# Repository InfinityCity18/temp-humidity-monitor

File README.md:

# Temperature and humidity HTTP monitor

A device that sends data about temperature and humidity to a HTTP server.
Also shows it on the lcd in daylight.

wokwi: https://wokwi.com/projects/406248125121901569

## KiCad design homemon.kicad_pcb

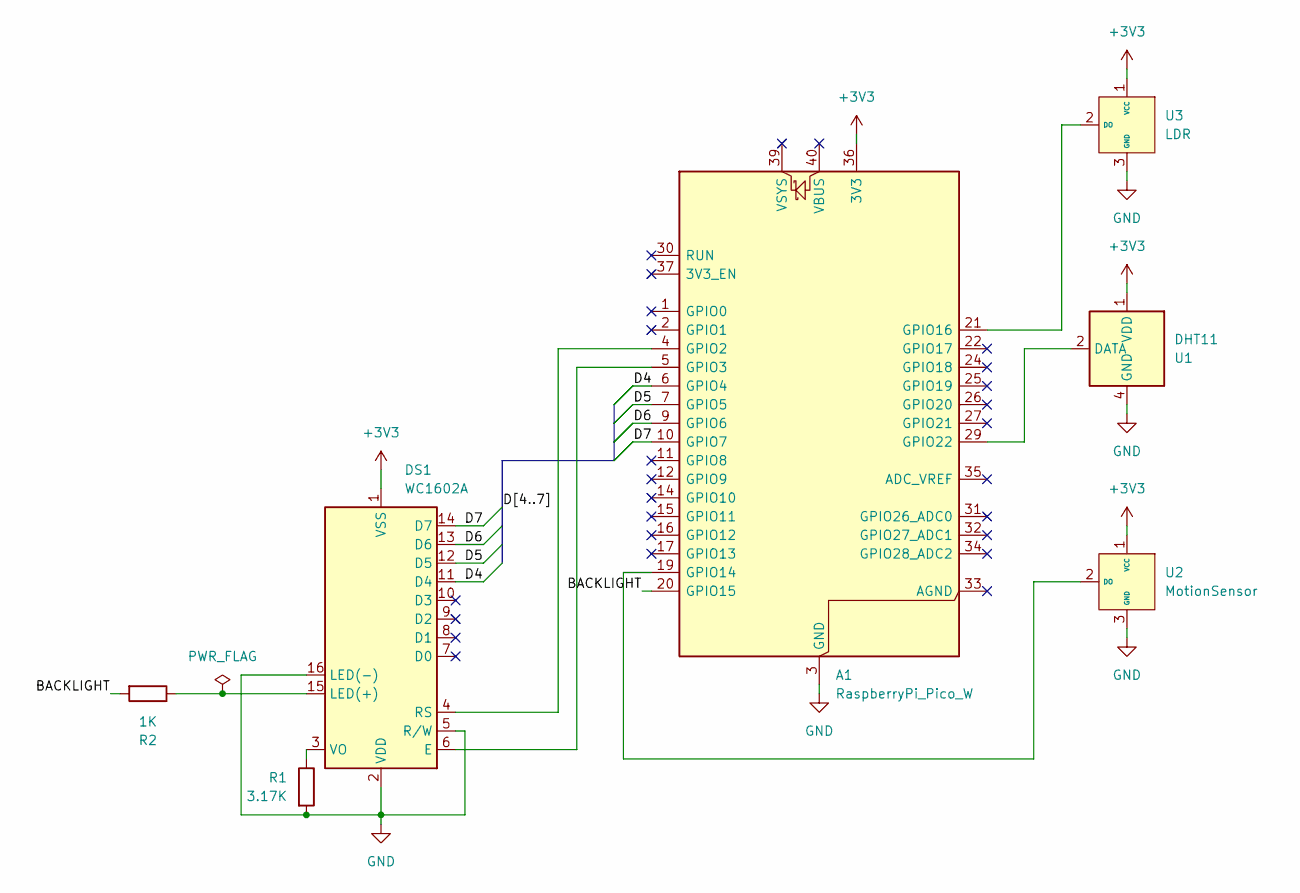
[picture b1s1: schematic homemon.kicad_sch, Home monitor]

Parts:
A1: RaspberryPi_Pico_W; RaspberryPi_Pico_Common_THT
DS1: WC1602A
R1: 3.17K; R_Axial_DIN0207_L6.3mm_D2.5mm_P10.16mm_Horizontal
R2: 1K; R_Axial_DIN0207_L6.3mm_D2.5mm_P10.16mm_Horizontal
U1: DHT11; PinHeader_1x03_P2.54mm_Vertical
U2: MotionSensor
U3: LDR; PinHeader_1x03_P2.54mm_Vertical

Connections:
+3V3: A1.36 (3V3), DS1.1 (VSS), U1.1 (VDD), U2.1 (VCC), U3.1 (VCC)
/BACKLIGHT: A1.20 (GPIO15), R2.2
/D4: A1.6 (GPIO4), DS1.11 (D4)
/D5: A1.7 (GPIO5), DS1.12 (D5)
/D6: A1.9 (GPIO6), DS1.13 (D6)
/D7: A1.10 (GPIO7), DS1.14 (D7)
GND: A1.3 (GND), A1.8 (GND), A1.13 (GND), A1.18 (GND), A1.23 (GND), A1.28 (GND), A1.38 (GND), DS1.2 (VDD), DS1.5 (R/W), DS1.16 (LED(-)), R1.2, U1.4 (GND), U2.3 (GND), U3.3 (GND)
unnamed: A1.4 (GPIO2), DS1.4 (RS)
unnamed: A1.5 (GPIO3), DS1.6 (E)
unnamed: A1.19 (GPIO14), U2.2 (DO)
unnamed: A1.21 (GPIO16), U3.2 (DO)
unnamed: A1.29 (GPIO22), U1.2 (DATA)
unnamed: DS1.15 (LED(+)), R2.1
unnamed: DS1.3 (VO), R1.1

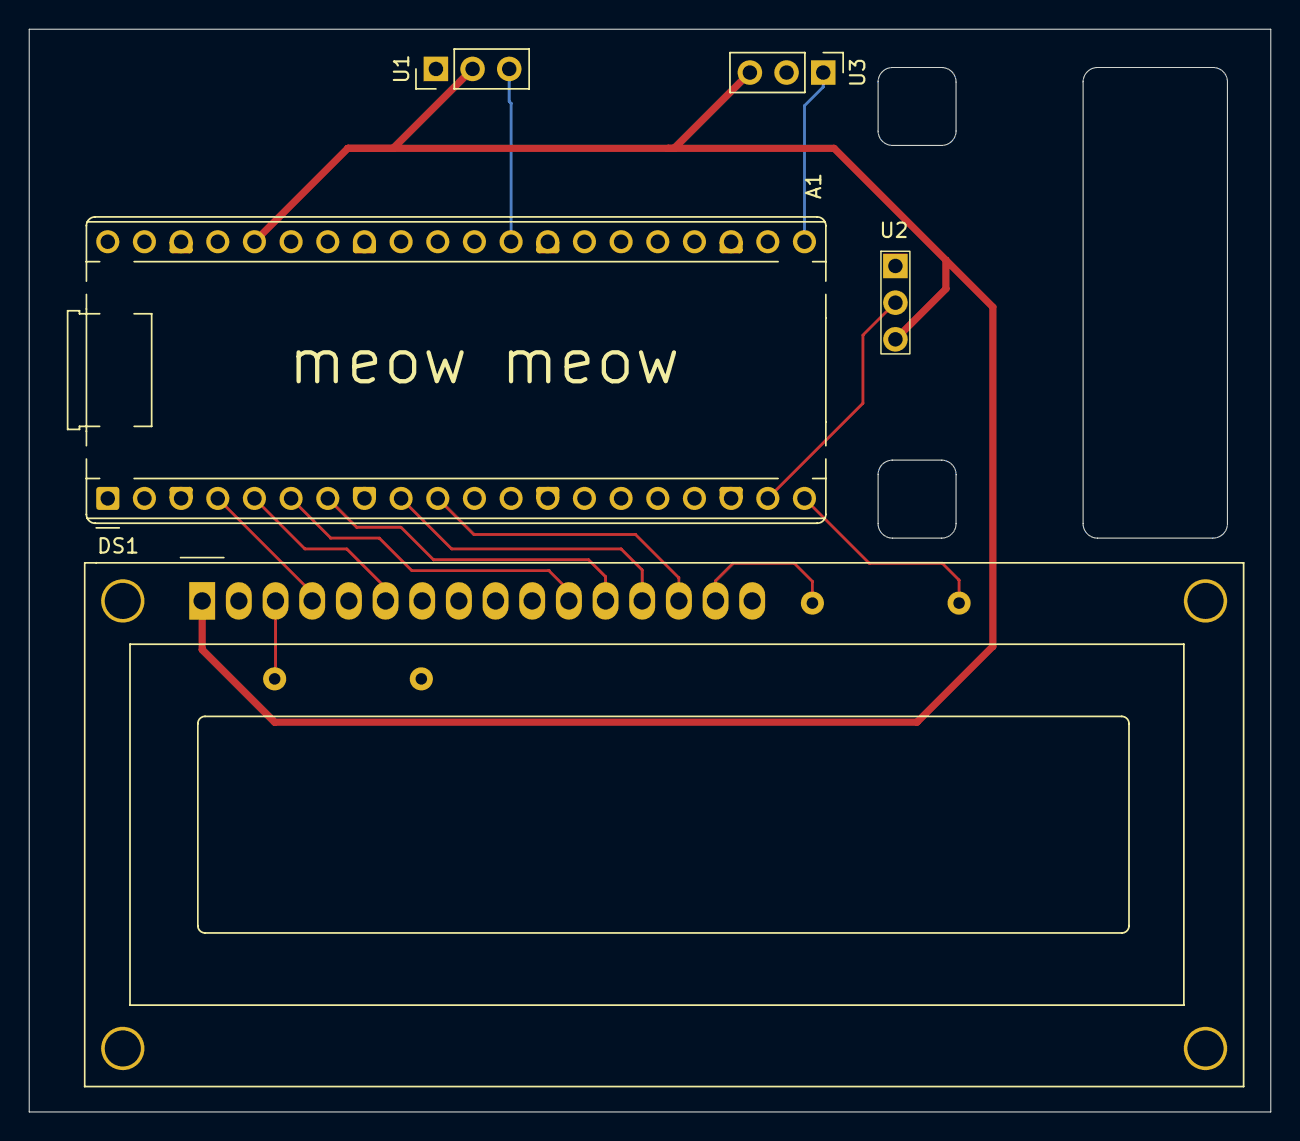
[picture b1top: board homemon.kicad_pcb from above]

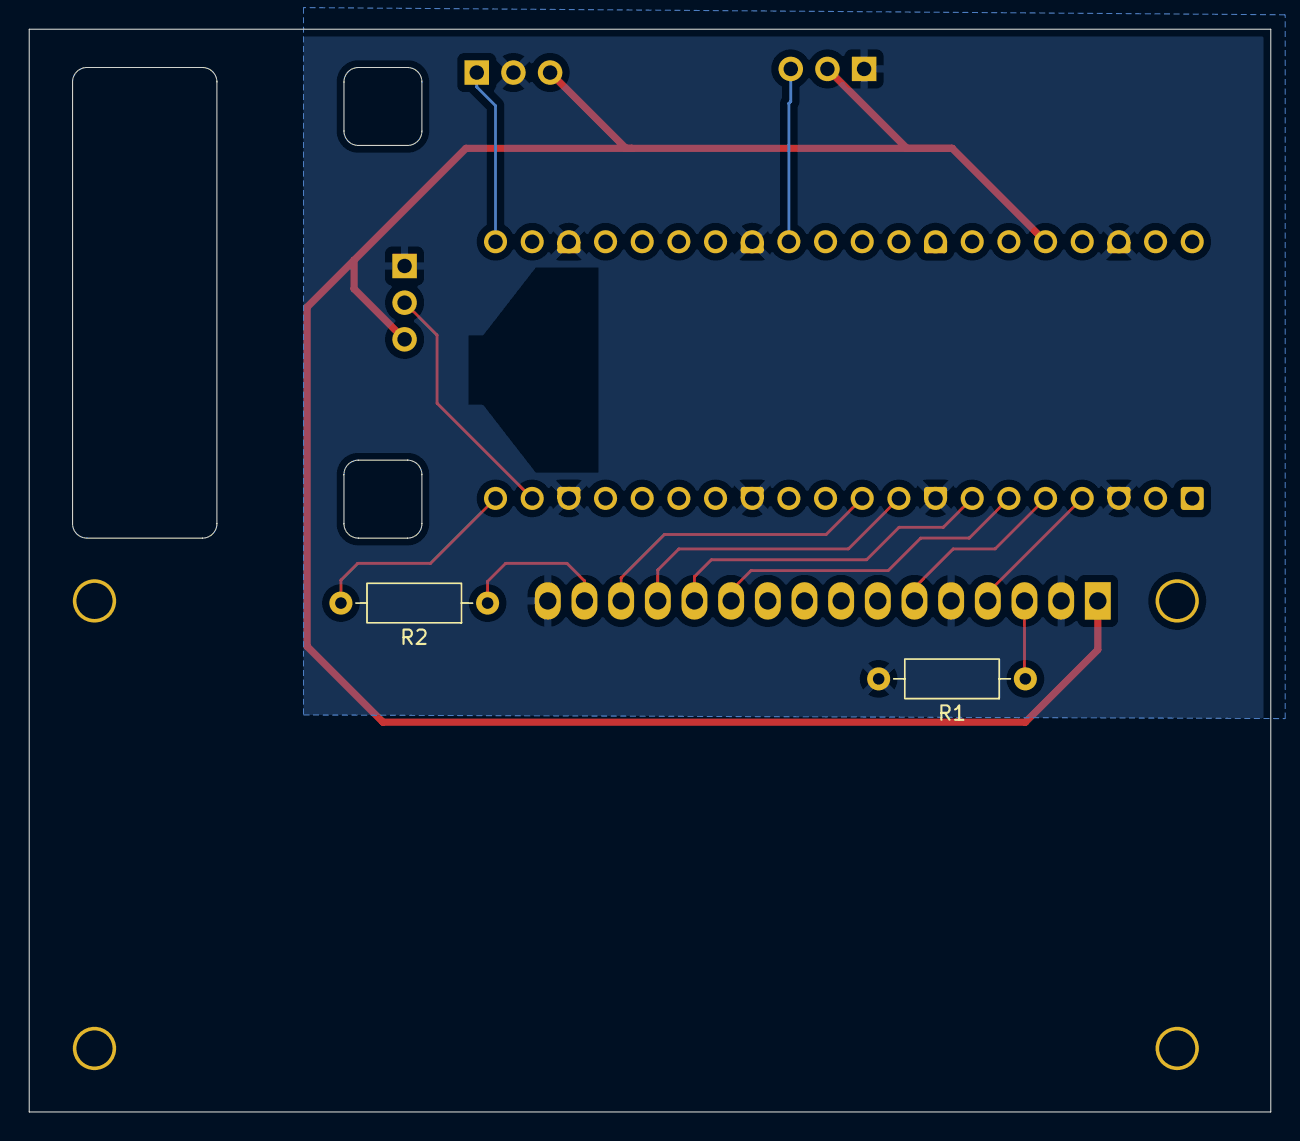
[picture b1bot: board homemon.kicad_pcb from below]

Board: 2 copper layers, 86.0 x 75.0 mm, 7 parts (2 on the bottom side), 14 nets.

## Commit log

2024-08-15 init
2024-08-15 added http
2024-08-20 Rename 2024-08-20-004025_hyprshot.png to preview.png
2026-03-05 Update host variable for network connection
2026-03-15 pin changes
2026-03-15 pcb files
